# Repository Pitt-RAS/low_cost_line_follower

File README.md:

#Low Cost Line Follower

The RAS club created a low cost line follower to provide beginners with an easy avenue to learn about Arduino and basic robotics.  This code is meant to be used as a starting point

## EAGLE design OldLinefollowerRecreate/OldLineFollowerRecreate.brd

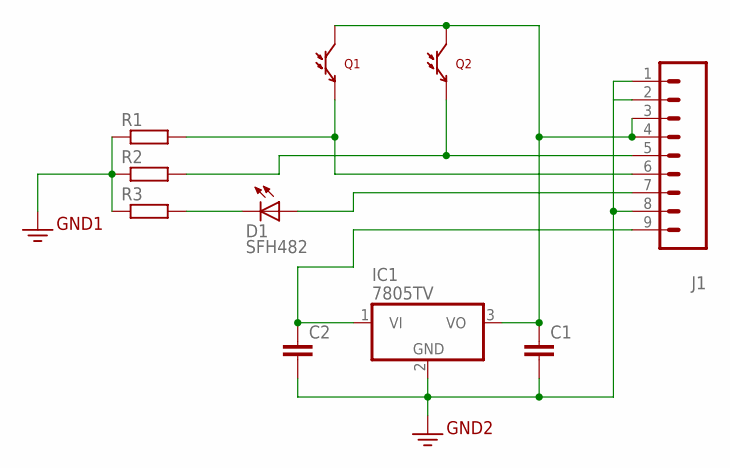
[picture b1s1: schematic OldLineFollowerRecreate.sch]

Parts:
C1, C2: C2.5/5; C2.5-5
D1: SFH482
IC1: 7805TV; TO220V
J1: M09; 1X09
Q1, Q2: LTR-301
R1, R2, R3: R0204/7; 0204/7

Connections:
3.3V: C1.2, C2.2, IC1.2 (GND), J1.1, J1.2, J1.8, R1.1, R2.1, R3.1
unnamed: C2.1, IC1.1 (VI), J1.9
unnamed: C1.1, IC1.3 (VO), J1.3, J1.4, Q1.C, Q2.C
unnamed: D1.K (C), R3.2
unnamed: D1.A, J1.7
unnamed: J1.6, Q1.E, R1.2
unnamed: J1.5, Q2.E, R2.2

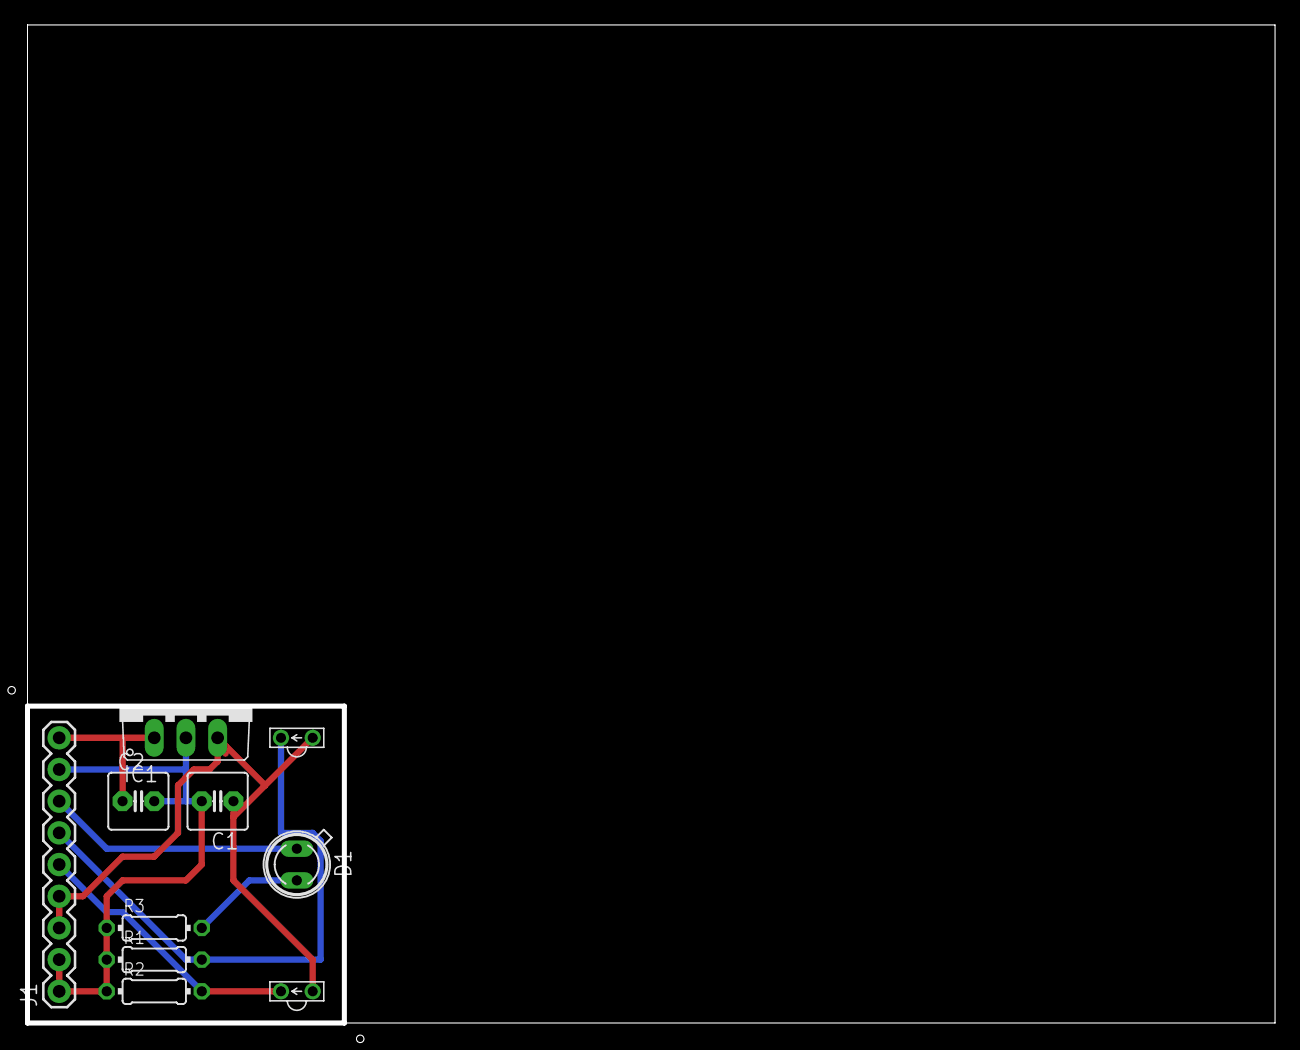
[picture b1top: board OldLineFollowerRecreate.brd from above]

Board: 2 copper layers, 100.0 x 80.0 mm, 10 parts (0 on the bottom side), 7 nets.

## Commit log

2016-01-17 Initial Commit
    Simply compares the left and right sensors and moves towards the darker
    one to stay centered on a dark line
2016-01-17 Updated code to use a threshold value
    Threshold value was found to be more reliable because the right and
    left sensors didn’t always read close enough values to be reliable.
2016-01-17 Created self adjusting sensor threshold
    The sensor threshold now updates itself by constantly checking if the
    current reading is lower than the minimum value recorded or higher than
    the max value recorded. If it is, the min and max values are reset and
    the threshold is set to the average of the two readings. The threshold
    starts as 100 based on tests using this setup.
2016-01-17 Added ReadMe
2016-09-01 Eagle files for circuit board, includes gcode

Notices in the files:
parts and their libraries:
SparkFun-Connectors: Licensing: Creative Commons ShareAlike 4.0 International - https://creativecommons.org/licenses/by-sa/4.0
